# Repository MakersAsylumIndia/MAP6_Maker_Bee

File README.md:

# MAP6
Honey Bee shaped course ware for Maker's Asylum Electronics course.

**Maker's Asylum Project #6**

***FEATURES***

1. Two LED's with series current limit resistors
2. Two CR2032 Coin Battery or two CR2016 cells in a single 2032 holder
3. Vibration motor to move the honey bee.
4. 555 timer controls current flowing through transistor, resulting in "breathing LED" effect
5. Vibration motor intensity changes in sync with LED effect.
6. Use 555 as astable multivibrator with minor mods (see schematic)

***LEARN***

1. How to Solder
2. Resistor Color Code
3. Use of Multimeter to check LED, Resistor and Battery

SET UP A LINK -> DISCUSSION FORUM : http://discuss.makersasylum.com/t/map4-makers-asylum-learn-to-solder-badge/123

**Renders**

**Animation**

## OSHWA Certification

The **MAP6** "Maker Bee" is "Open Source Hardware" as certified by the [OSHWA](https://certification.oshwa.org/in000031.html).
OSHWA UID for the M19O2 is **IN000031**

<a href="https://certification.oshwa.org/in000031.html">

License
-------

[CERN Open Hardware Licence v1.2 ]

[CERN Open Hardware Licence v1.2 ]:http://www.ohwr.org/attachments/2388/cern_ohl_v_1_2.txt

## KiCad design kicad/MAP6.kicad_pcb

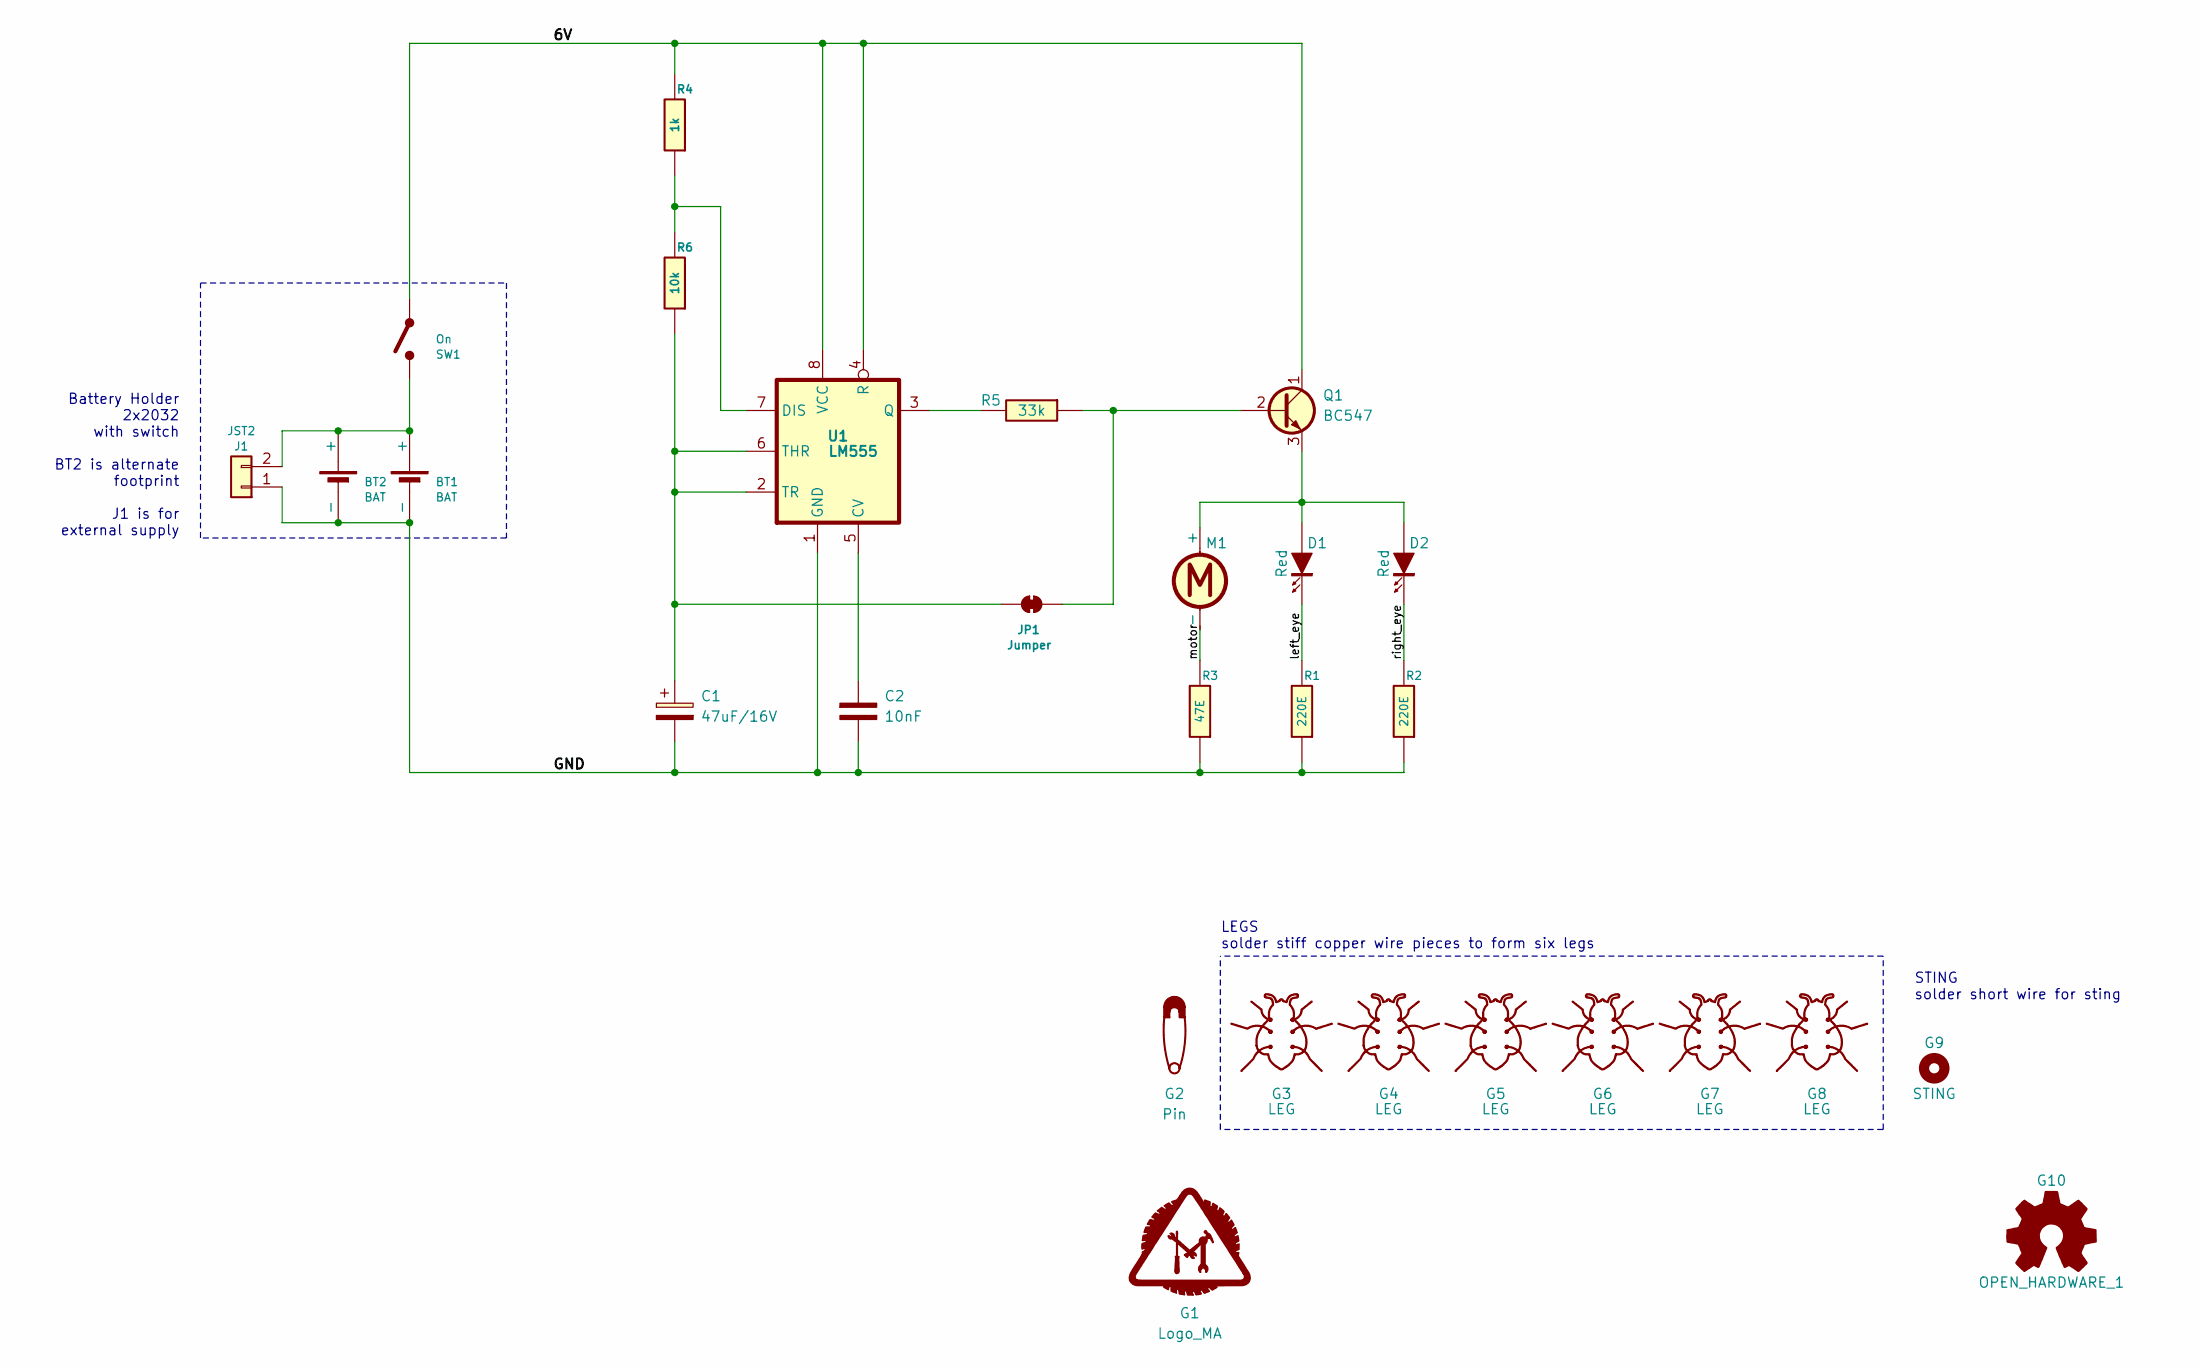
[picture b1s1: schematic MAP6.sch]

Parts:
BT1: BAT; cr2032_03
BT2: BAT; cr2032_04_3025-2
C1: 47uF/16V; CP_Radial_D6.3mm_P2.50mm
C2: 10nF; C_Disc_D5.0mm_W2.5mm_P2.50mm
D1: Red; LED-5MM_left
D2: Red; LED-5MM_right
G1: Logo_MA; MA_LOGO
G2: Pin; MTG_2mm
G3, G4, G5, G6, G7, G8: LEG; MTG_1mm
G9: STING; MTG_0mm8
G10: OPEN_HARDWARE_1; Logo_silk_OSHW_6x6mm
J1: JST2; JST_EH_B2B-EH-A_1x02_P2.50mm_Vertical
JP1: Jumper; SolderJumper-2_P1.3mm_Bridged2Bar_RoundedPad1.0x1.5mm
M1: Motor; motor_XDCR_C0720B001F
Q1: BC547; TO-92L_Wide
R1, R2: 220E; r_0805
R3: 47E; r_0805
R4: 1k; r_0805
R5: 33k; r_0805
R6: 10k; r_0805
SW1: On; SW_SPDT_Straight
U1: LM555; DIP-8_W7.62mm

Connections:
/6V: Q1.1 (C), R4.2, SW1.1 (A), U1.4 (R), U1.8 (VCC)
/GND: BT1.2 (-), BT2.2 (-), C1.2, C2.2, J1.1, R1.1, R2.1, R3.1, U1.1 (GND)
/left_eye: D1.2 (K), R1.2
/motor: M1.2 (-), R3.2
/right_eye: D2.2 (K), R2.2
unnamed: BT1.1 (+), BT2.1 (+), J1.2, SW1.2 (B)
unnamed: C1.1, JP1.1 (A), R6.1, U1.2 (TR), U1.6 (THR)
unnamed: C2.1, U1.5 (CV)
unnamed: D1.1 (A), D2.1 (A), M1.1 (+), Q1.3 (E)
unnamed: JP1.2 (B), Q1.2 (B), R5.1
unnamed: R4.1, R6.2, U1.7 (DIS)
unnamed: R5.2, U1.3 (Q)

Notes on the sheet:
Battery Holder 2x2032 with switch BT2 is alternate footprint J1 is for external supply
LEGS solder stiff copper wire pieces to form six legs
STING solder short wire for sting

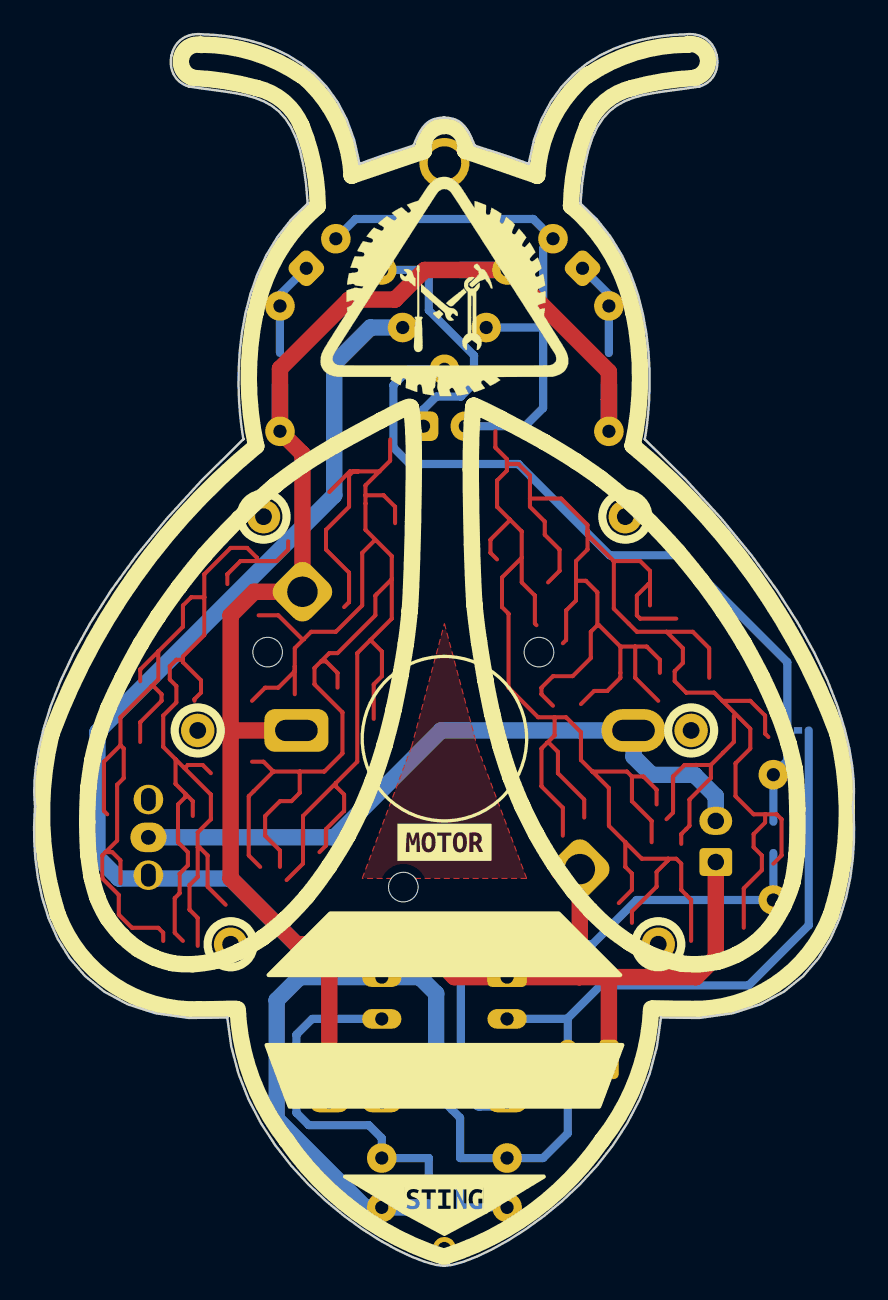
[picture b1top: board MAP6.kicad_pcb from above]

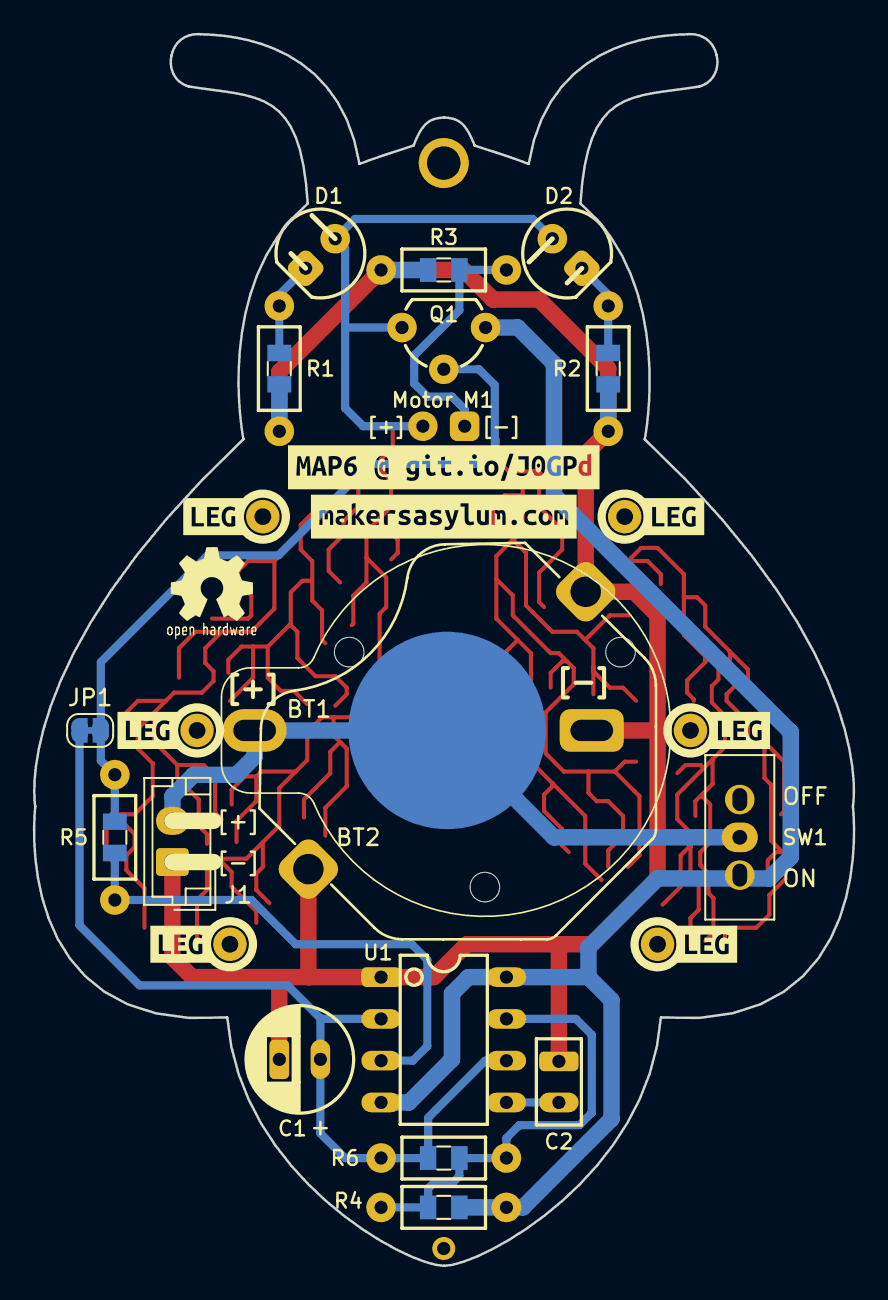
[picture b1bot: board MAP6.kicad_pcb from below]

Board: 2 copper layers, 49.9 x 74.9 mm, 38 parts (32 on the bottom side), 12 nets.

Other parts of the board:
kibuzzard-611CD92E: G***; label_website
kibuzzard-611CDC95, kibuzzard-611CDC95#2, kibuzzard-611CDC95#3, kibuzzard-611CDC95#4, kibuzzard-611CDC95#5, kibuzzard-611CDC95#6: G***; label_LEG
kibuzzard-611CE09C: G***; label_sting
kibuzzard-611CF906: G***; label_URL
kibuzzard-612E1065: G***; label

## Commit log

2021-08-18 M19O2 MAP6 initial commit
2021-08-18 Update README.md
    edited image links
2021-08-18 M19O2 MAP6 added .STEP CAD file
2021-08-18 M19O2 MAP6 cleaned SILK legend
2021-08-23 MAP6 Blender renders and amimations
2021-08-24 added interactive HTML BoM in /bom folder
2021-08-31 updated schematic and pcb
2021-09-06 Create readme.md
    added link for online BoM
2021-09-06 added animated gif
2021-09-07 big update, added several battery options
2021-09-07 readme update
2021-09-08 another big update after deciding battery options. Ready for FAB
2021-10-22 added assembly images in /fabricate folder
2021-10-31 added OSHWA certification details
2023-02-06 added production files folder, LCSC BoM
